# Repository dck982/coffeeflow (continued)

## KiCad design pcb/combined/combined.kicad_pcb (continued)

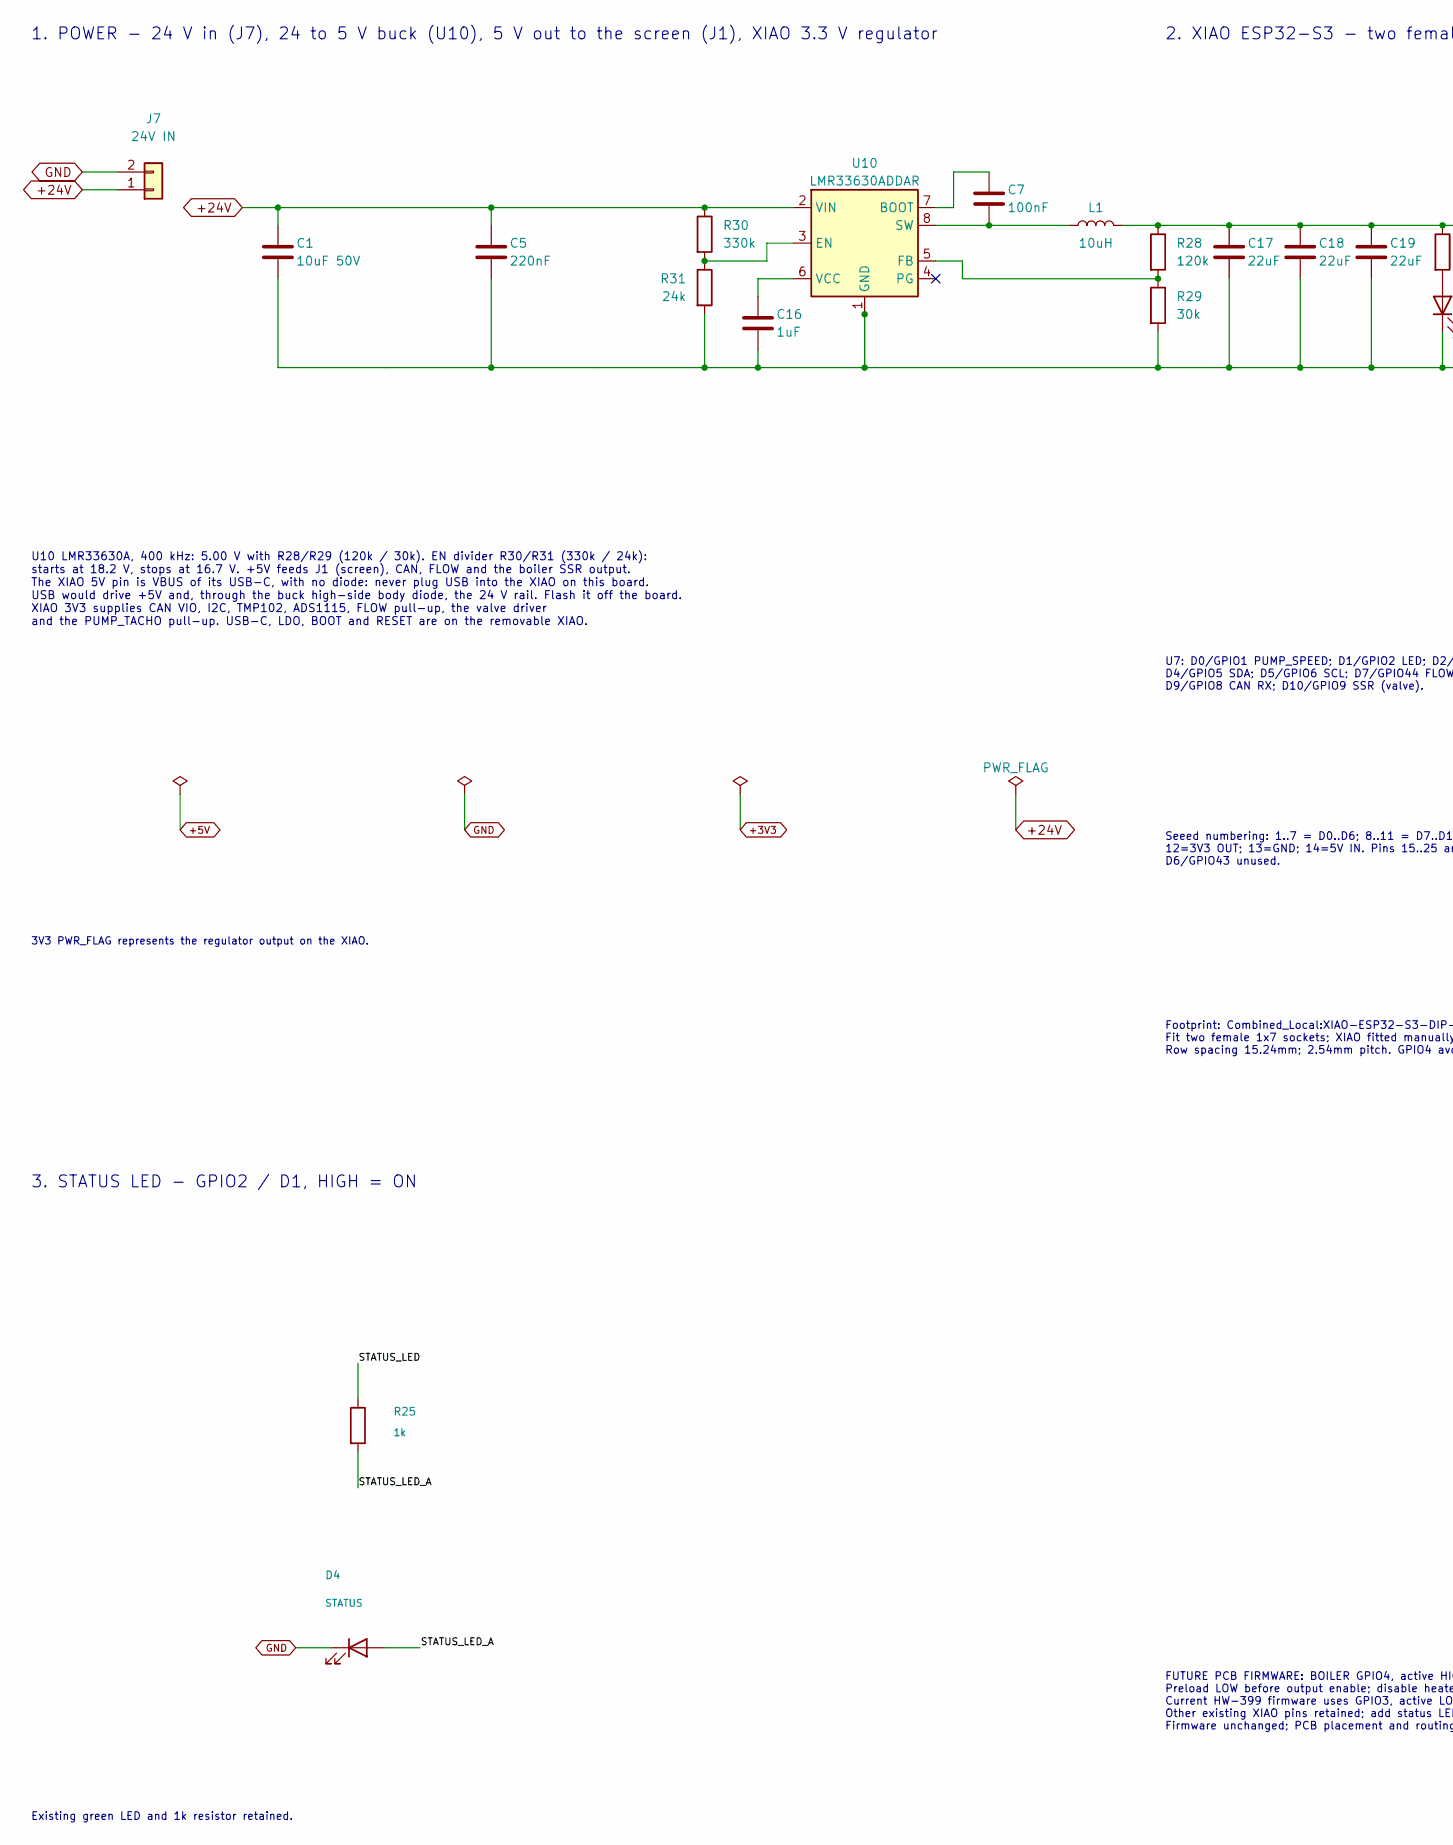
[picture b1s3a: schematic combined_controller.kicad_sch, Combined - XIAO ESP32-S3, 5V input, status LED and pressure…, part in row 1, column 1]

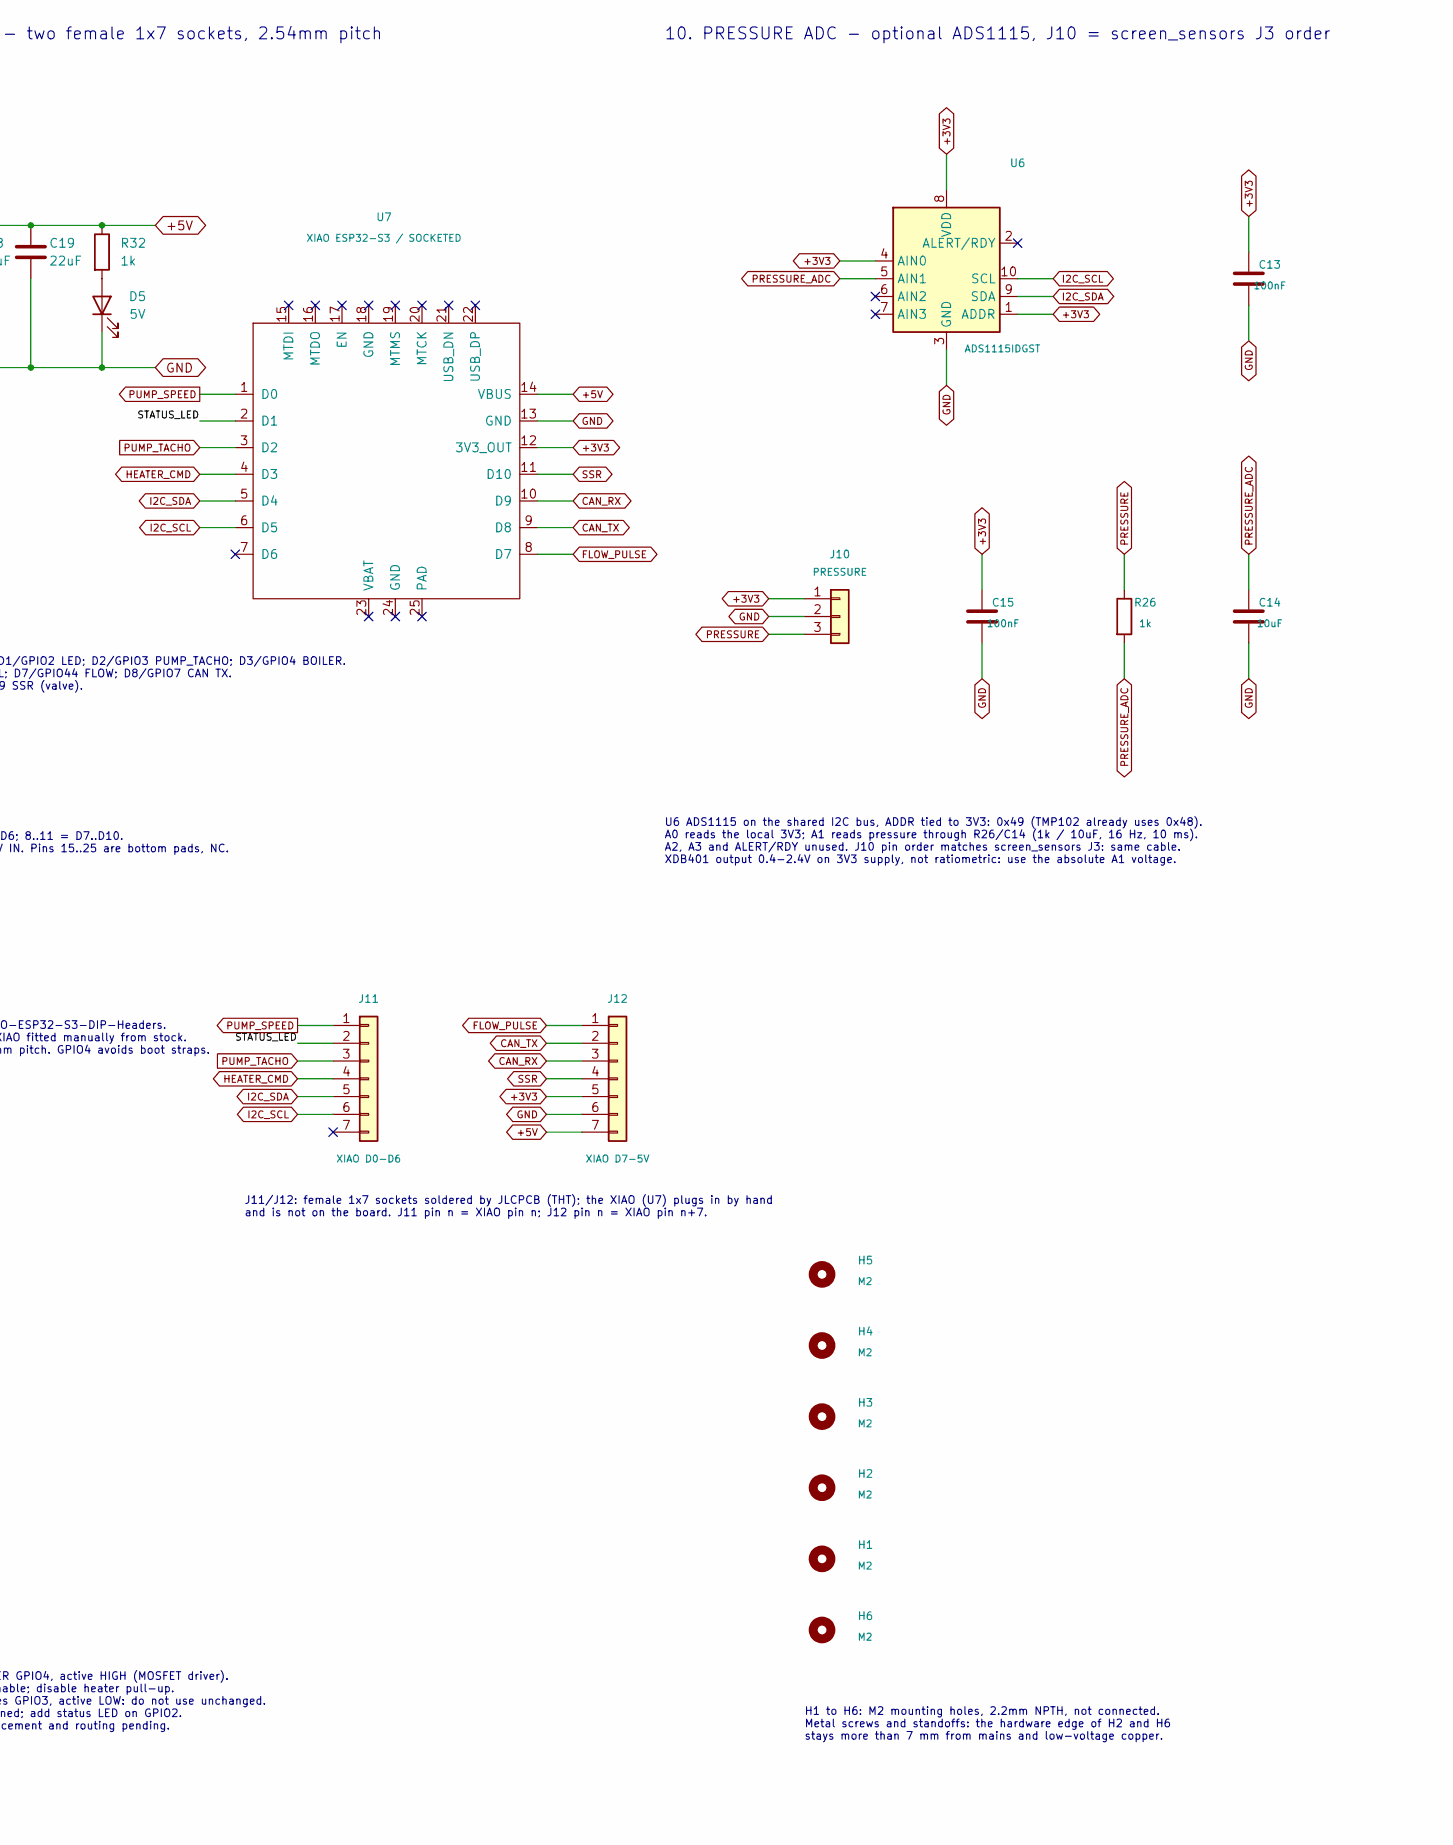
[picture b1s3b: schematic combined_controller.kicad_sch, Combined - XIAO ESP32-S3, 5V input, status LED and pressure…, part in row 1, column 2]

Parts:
C1: 10uF 50V; C_1206_3216Metric; MPN CL31A106KBHNNNE; LCSC C13585
C5: 220nF; C_0805_2012Metric; MPN CL21B224KBFNNNE; LCSC C5378
C7, C13, C15: 100nF; C_0603_1608Metric; MPN CC0603KRX7R9BB104; LCSC C14663
C14: 10uF; C_0603_1608Metric; MPN CL10A106KP8NNNC; LCSC C19702
C16: 1uF; C_0603_1608Metric; MPN CL10A105KB8NNNC; LCSC C15849
C17, C18, C19: 22uF; C_1206_3216Metric; MPN CL31A226KAHNNNE; LCSC C12891
D4: STATUS; LED_0603_1608Metric; MPN KT-0603R; LCSC C2286
D5: 5V; LED_0603_1608Metric; MPN KT-0603R; LCSC C2286
H1, H2, H3, H4, H5, H6: M2; MountingHole_2.2mm_M2; MPN M2 / 2.2mm
J7: 24V IN; CONN-TH_P3.96_HT396V-3.96-2P; MPN HT396V-3.96-2P; LCSC C577788
J10: PRESSURE; JST_XH_B3B-XH-A_1x03_P2.50mm_Vertical; MPN B3B-XH-A(LF)(SN); LCSC C144394
J11: XIAO D0-D6; XIAO_Socket_1x07_P2.54mm_Vertical; MPN HC-PM254-5.0H-1x7PZ; LCSC C27985232
J12: XIAO D7-5V; XIAO_Socket_1x07_P2.54mm_Vertical; MPN HC-PM254-5.0H-1x7PZ; LCSC C27985232
L1: 10uH; L_Changjiang_FXL0630; MPN FXL0630-100-M; LCSC C167223
R25, R26, R32: 1k; R_0603_1608Metric; MPN 0603WAF1001T5E; LCSC C21190
R28: 120k; R_0603_1608Metric; MPN 0603WAF1203T5E; LCSC C25808
R29: 30k; R_0603_1608Metric; MPN 0603WAF3002T5E; LCSC C22984
R30: 330k; R_0603_1608Metric; MPN 0603WAF3303T5E; LCSC C23137
R31: 24k; R_0603_1608Metric; MPN 0603WAF2402T5E; LCSC C23352
U6: ADS1115IDGST; TSSOP-10_3x3mm_P0.5mm; MPN ADS1115IDGST; LCSC C468683
U7: XIAO ESP32-S3 / SOCKETED; XIAO-ESP32-S3-DIP-Headers; MPN Seeed Studio XIAO ESP32-S3
U10: LMR33630ADDAR; Texas_HSOP-8-1EP_3.9x4.9mm_P1.27mm_ThermalVias; MPN LMR33630ADDAR; LCSC C841384

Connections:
+3V3: C13.1, C15.1, J10.1, J12.5, U6.1 (ADDR), U6.4 (AIN0), U6.8 (VDD), U7.12 (3V3_OUT); also elsewhere on the board
+5V: C17.1, C18.1, C19.1, J12.7, L1.2, R28.1, R32.1, U7.14 (VBUS); also elsewhere on the board
+24V: C1.1, C5.1, J7.1, R30.1, U10.2 (VIN)
/Controller/STATUS_LED: J11.2, R25.1, U7.2 (D1)
/Controller/STATUS_LED_A: D4.2 (A), R25.2
CAN_RX: J12.3, U7.10 (D9); also elsewhere on the board
CAN_TX: J12.2, U7.9 (D8); also elsewhere on the board
FLOW_PULSE: J12.1, U7.8 (D7); also elsewhere on the board
GND: C1.2, C5.2, C13.2, C14.2, C15.2, C16.2, C17.2, C18.2, C19.2, D4.1 (K), D5.1 (K), J7.2, J10.2, J12.6, R29.2, R31.2, U6.3 (GND), U7.13 (GND), U10.1 (GND), U10.9 (GND); also elsewhere on the board
HEATER_CMD: J11.4, U7.4 (D3); also elsewhere on the board
I2C_SCL: J11.6, U6.10 (SCL), U7.6 (D5); also elsewhere on the board
I2C_SDA: J11.5, U6.9 (SDA), U7.5 (D4); also elsewhere on the board
unnamed: D5.2 (A), R32.2
unnamed: C7.1, U10.7 (BOOT)
unnamed: R30.2, R31.1, U10.3 (EN)
unnamed: R28.2, R29.1, U10.5 (FB)
unnamed: C7.2, L1.1, U10.8 (SW)
unnamed: C16.1, U10.6 (VCC)
PRESSURE: J10.3, R26.1
PRESSURE_ADC: C14.1, R26.2, U6.5 (AIN1)
PUMP_SPEED: J11.1, U7.1 (D0); also elsewhere on the board
PUMP_TACHO: J11.3, U7.3 (D2); also elsewhere on the board
SSR: J12.4, U7.11 (D10); also elsewhere on the board

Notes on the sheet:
Footprint: Combined_Local:XIAO-ESP32-S3-DIP-Headers. Fit two female 1x7 sockets; XIAO fitted manually from stock. Row spacing 15.24mm; 2.54mm pitch. GPIO4 avoids boot straps.
Existing green LED and 1k resistor retained.
U7: D0/GPIO1 PUMP_SPEED; D1/GPIO2 LED; D2/GPIO3 PUMP_TACHO; D3/GPIO4 BOILER. D4/GPIO5 SDA; D5/GPIO6 SCL; D7/GPIO44 FLOW; D8/GPIO7 CAN TX. D9/GPIO8 CAN RX; D10/GPIO9 SSR (valve).
1. POWER - 24 V in (J7), 24 to 5 V buck (U10), 5 V out to the screen (J1), XIAO 3.3 V regulator
3. STATUS LED - GPIO2 / D1, HIGH = ON
3V3 PWR_FLAG represents the regulator output on the XIAO.
10. PRESSURE ADC - optional ADS1115, J10 = screen_sensors J3 order
U10 LMR33630A, 400 kHz: 5.00 V with R28/R29 (120k / 30k). EN divider R30/R31 (330k / 24k): starts at 18.2 V, stops at 16.7 V. +5V feeds J1 (screen), CAN, FLOW and the boiler SSR output. The XIAO 5V pin is VBUS of its USB-C, with no diode: never plug USB into the XIAO on this board. USB would drive 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
FUTURE PCB FIRMWARE: BOILER GPIO4, active HIGH (MOSFET driver). Preload LOW before output enable; disable heater pull-up. Current HW-399 firmware uses GPIO3, active LOW: do not use unchanged. Other existing XIAO pins retained; add status LED on GPIO2. Firmware unchanged; PCB placement and routing p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
J11/J12: female 1x7 sockets soldered by JLCPCB (THT); the XIAO (U7) plugs in by hand and is not on the board. J11 pin n = XIAO pin n; J12 pin n = XIAO pin n+7.
Seeed numbering: 1..7 = D0..D6; 8..11 = D7..D10. 12=3V3 OUT; 13=GND; 14=5V IN. Pins 15..25 are bottom pads, NC. D6/GPIO43 unused.
U6 ADS1115 on the shared I2C bus, ADDR tied to 3V3: 0x49 (TMP102 already uses 0x48). A0 reads the local 3V3; A1 reads pressure through R26/C14 (1k / 10uF, 16 Hz, 10 ms). A2, A3 and ALERT/RDY unused. J10 pin order matches screen_sensors J3: same cable. XDB401 output 0.4-2.4V on 3V3 supply, not ratio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
H1 to H6: M2 mounting holes, 2.2mm NPTH, not connected. Metal screws and standoffs: the hardware edge of H2 and H6 stays more than 7 mm from mains and low-voltage copper.
2. XIAO ESP32-S3 - two female 1x7 sockets, 2.54mm pitch

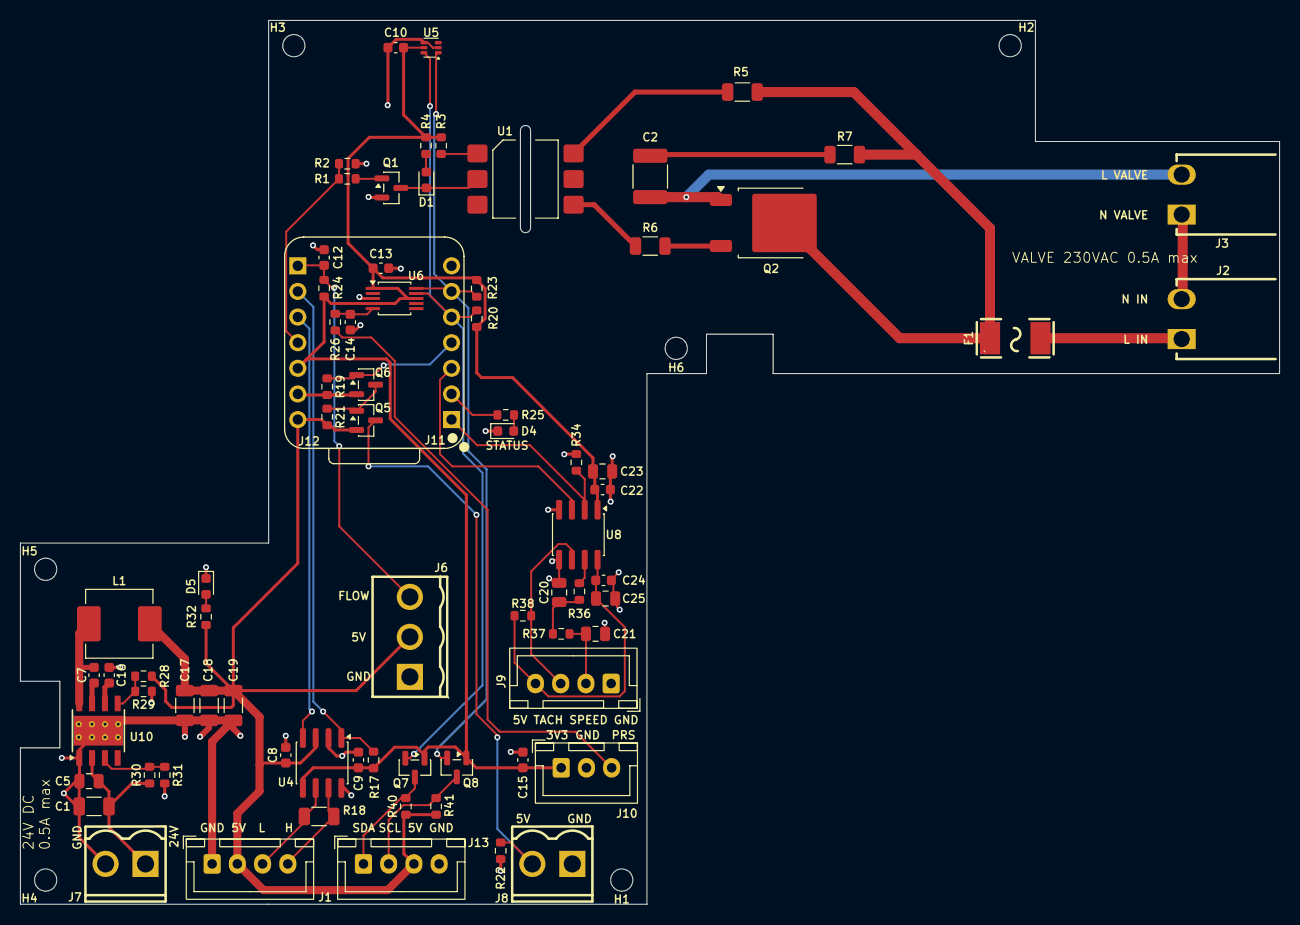
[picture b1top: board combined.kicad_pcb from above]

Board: 2 copper layers, 124.8 x 87.6 mm, 84 parts (0 on the bottom side), 47 nets.

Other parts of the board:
XIAO: XIAO-ESP32-S3-Outline

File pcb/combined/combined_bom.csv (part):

"Reference","Value","Footprint","DNP","MPN","LCSC","Note"
"C1","10uF 50V","Capacitor_SMD:C_1206_3216Metric","","CL31A106KBHNNNE","C13585","VIN ceramic, X5R 50 V 1206"
"C2","10nF 1kV","Capacitor_SMD:C_1812_4532Metric","","FV43X103K102EFG","C394164","Snubber, X7R 1000 V"
"C5","220nF","Capacitor_SMD:C_0805_2012Metric","","CL21B224KBFNNNE","C5378","VIN high-frequency bypass, 50 V X7R 0805, next to the VIN and PGND pins"
"C7","100nF","Capacitor_SMD:C_0603_1608Metric","","CC0603KRX7R9BB104","C14663","BOOT to SW"
"C8","100nF","Capacitor_SMD:C_0603_1608Metric","","CC0603KRX7R9BB104","C14663","Unpolarized capacitor"
"C9","100nF","Capacitor_SMD:C_0603_1608Metric","","CC0603KRX7R9BB104","C14663","Unpolarized capacitor"
"C10","100nF","Capacitor_SMD:C_0603_1608Metric","","CC0603KRX7R9BB104","C14663","Unpolarized capacitor"
"C12","10nF","Capacitor_SMD:C_0603_1608Metric","","0603B103K500NT","C57112","Unpolarized capacitor"
"C13","100nF","Capacitor_SMD:C_0603_1608Metric","","CC0603KRX7R9BB104","C14663","100nF 50V X7R 0603; U6 ADS1115 decoupling."
"C14","10uF","Capacitor_SMD:C_0603_1608Metric","","CL10A106KP8NNNC","C19702","10uF 10V X5R 0603; pressure input filter with R26 (16 Hz)."
"C15","100nF","Capacitor_SMD:C_0603_1608Metric","","CC0603KRX7R9BB104","C14663","100nF 50V X7R 0603; decoupling at the J10 pressure sensor supply."
"C16","1uF","Capacitor_SMD:C_0603_1608Metric","","CL10A105KB8NNNC","C15849","VCC (internal LDO) decoupling"
"C17","22uF","Capacitor_SMD:C_1206_3216Metric","","CL31A226KAHNNNE","C12891","Output ceramic, X5R 25 V 1206"
"C18","22uF","Capacitor_SMD:C_1206_3216Metric","","CL31A226KAHNNNE","C12891","Output ceramic, X5R 25 V 1206"
"C19","22uF","Capacitor_SMD:C_1206_3216Metric","","CL31A226KAHNNNE","C12891","Output ceramic, X5R 25 V 1206"
"C20","2.2uF","Capacitor_SMD:C_0805_2012Metric","","CL21A225KBQNNNE","C377773","Setpoint filter, 50 V X5R"
"C21","2.2uF","Capacitor_SMD:C_0805_2012Metric","","CL21A225KBQNNNE","C377773","Setpoint filter, 50 V X5R"
"C22","100nF","Capacitor_SMD:C_0603_1608Metric","","CC0603KRX7R9BB104","C14663","U8 VDDA (3V3) decoupling, at pin 1"
"C23","1uF","Capacitor_SMD:C_0805_2012Metric","","CL21B105KBFNNNE","C28323","U8 VDDA (3V3) decoupling, next to C22"
"C24","100nF","Capacitor_SMD:C_0603_1608Metric","","CC0603KRX7R9BB104","C14663","U8 VDDB (pump 5 V) decoupling, at pin 8"
"C25","1uF","Capacitor_SMD:C_0805_2012Metric","","CL21B105KBFNNNE","C28323","U8 VDDB (pump 5 V) decoupling, next to C24"
"D1","RED","LED_SMD:LED_0603_1608Metric","","KT-0603R","C2286","Channel indicator"
"D4","STATUS","LED_SMD:LED_0603_1608Metric","","KT-0603R","C2286","Red 0603, as D1 and D2; pin 1 cathode to GND, pin 2 anode via R25 (1k) from GPIO2."
"D5","5V","LED_SMD:LED_0603_1608Metric","","KT-0603R","C2286","Red 0603, lit while +5V is up"
"F1","0.5A 250V fast","Combined_Local:F2410","","MF2410F0.500TM","C91409","AEM 2410 fast, 100 A breaking at 250 VAC; valve only (65 mA)"
"J1","SCREEN","Connector_JST:JST_XH_B4B-XH-A_1x04_P2.50mm_Vertical","","B4B-XH-A(LF)(SN)","C144395","5 V and CAN to the screen, one cable: 1 GND, 2 +5V, 3 CAN_L, 4 CAN_H"
"J2","MAINS_IN","Combined_Local:CONN-TH_P3.96_HT396R-3.96-2P","","MXHT396R-3.96-02P-OE01-Cu-A","C48688287","1 L, 2 N"
"J3","VALVE","Combined_Local:CONN-TH_P3.96_HT396R-3.96-2P","","MXHT396R-3.96-02P-OE01-Cu-A","C48688287","1 N, 2 L (switched): N next to N of J2"
"J6","FLOW HALL","Combined_Local:CONN-TH_P3.96_HT396V-3.96-3P","","HT396V-3.96-3P","C577789","Kefa HT396V vertical header; mating plug HT396K-3.96-3P (C577778, screw) takes the 0.5 mm2 wires of the Digmesa cable: 1 GND, 2 +5V, 3 FLOW_PULSE"
"J7","24V IN","Combined_Local:CONN-TH_P3.96_HT396V-3.96-2P","","HT396V-3.96-2P","C577788","Kefa HT396V vertical header; mating plug HT396K-3.96-2P (C577777, screw), 1 +24V, 2 GND, from the Wago split of the 24 V supply"
"J8","BOILER SSR","Combined_Local:CONN-TH_P3.96_HT396V-3.96-2P","","HT396V-3.96-2P","C577788","Kefa HT396V vertical header; mating plug HT396K-3.96-2P (C577777, screw, up to 1.5 mm2) takes the 0.75 mm2 wires to the boiler SSR: 1 SSR (-), 2 SSR (+)"
"J9","PUMP","Connector_JST:JST_XH_B4B-XH-A_1x04_P2.50mm_Vertical","","B4B-XH-A(LF)(SN)","C144395","1 GND_P (green), 2 SPEED_P (brown), 3 TACHO_P (blue), 4 +5V_P (yellow); pump side only"
"J10","PRESSURE","Connector_JST:JST_XH_B3B-XH-A_1x03_P2.50mm_Vertical","","B3B-XH-A(LF)(SN)","C144394","Pressure sensor input: pin 1 3V3, 2 GND, 3 output."
"J11","XIAO D0-D6","Combined_Local:XIAO_Socket_1x07_P2.54mm_Vertical","","HC-PM254-5.0H-1x7PZ","C27985232","Female 1x7 2.54 mm socket, 5.0 mm high, for XIAO pins 1-7. Soldered by JLCPCB (THT); the XIAO plugs in by hand."
"J12","XIAO D7-5V","Combined_Local:XIAO_Socket_1x07_P2.54mm_Vertical","","HC-PM254-5.0H-1x7PZ","C27985232","Female 1x7 2.54 mm socket, 5.0 mm high, for XIAO pins 8-14. Soldered by JLCPCB (THT); the XIAO plugs in by hand."
"J13","SCALE","Connector_JST:JST_XH_B4B-XH-A_1x04_P2.50mm_Vertical","","B4B-XH-A(LF)(SN)","C144395","To the scale board J1 (screw terminal), pin for pin: 1 SCALE_SDA, 2 SCALE_SCL, 3 +5V, 4 GND; 5 V I2C to the NAU7802"
"L1","10uH","Inductor_SMD:L_Changjiang_FXL0630","","FXL0630-100-M","C167223","10 uH, 4.5 A saturation, 68 mOhm"
"Q1","SS8050","Package_TO_SOT_SMD:SOT-23","","SS8050 (Y1)","C2150","SOT-23 pinout 1 B, 2 E, 3 C"
"Q2","BT136S","Package_TO_SOT_SMD:TO-252-2","","BT136S","C23427","DPAK: 1 MT1, 2 MT2 (tab), 3 G"
"Q5","AO3401A","Package_TO_SOT_SMD:SOT-23","","AO3401A","C15127","-4.0A Id, -30V Vds, P-Channel MOSFET, SOT-23"
"Q6","2N7002","Package_TO_SOT_SMD:SOT-23","","2N7002","C8545","0.115A Id, 60V Vds, N-Channel MOSFET, SOT-23"
"Q7","BSS138","Package_TO_SOT_SMD:SOT-23","","BSS138-7-F","C40912","I2C_SDA level shifter, gate on +3V3: 3.3 V bus to SCALE_SDA (5 V)"
"Q8","BSS138","Package_TO_SOT_SMD:SOT-23","","BSS138-7-F","C40912","I2C_SCL level shifter, gate on +3V3: 3.3 V bus to SCALE_SCL (5 V)"
"R1","1k","Resistor_SMD:R_0603_1608Metric","","0603WAF1001T5E","C21190","Base resistor"
"R2","4.7k","Resistor_SMD:R_0603_1608Metric","","0603WAF4701T5E","C23162","Holds the valve channel off while the XIAO is absent or booting"
"R3","150","Resistor_SMD:R_0603_1608Metric","","0603WAF1500T5E","C22808","MOC LED: (3.3-1.2-0.1)/150 = 13 mA typ, >= 9.6 mA worst case"
"R4","1k","Resistor_SMD:R_0603_1608Metric","","0603WAF1001T5E","C21190","Indicator LED ~1.2 mA"
"R5","300","Resistor_SMD:R_1206_3216Metric","","1206W4F3000T5E","C17887","MT2 series resistor; R5 + R6 = 600 ohms"
"R6","300","Resistor_SMD:R_1206_3216Metric","","1206W4F3000T5E","C17887","Gate series resistor; R5 + R6 = 600 ohms"
"R7","100","Resistor_SMD:R_1206_3216Metric","","1206W4F1000T5E","C17901","Snubber"
"R17","10k","Resistor_SMD:R_0603_1608Metric","","0603WAF1002T5E","C25804","Resistor"
"R18","120 / 0.25W","Resistor_SMD:R_1206_3216Metric","","1206W4F1200T5E","C17909","Resistor"
"R19","100k","Resistor_SMD:R_0603_1608Metric","","0603WAF1003T5E","C25803","Resistor"
"R20","4.7k","Resistor_SMD:R_0603_1608Metric","","0603WAF4701T5E","C23162","Resistor"
"R21","10k","Resistor_SMD:R_0603_1608Metric","","0603WAF1002T5E","C25804","Resistor"
"R22","1k","Resistor_SMD:R_0603_1608Metric","","0603WAF1001T5E","C21190","Resistor"
"R23","4.7k","Resistor_SMD:R_0603_1608Metric","","0603WAF4701T5E","C23162","Resistor"
"R24","1k","Resistor_SMD:R_0603_1608Metric","","0603WAF1001T5E","C21190","Resistor"
"R25","1k","Resistor_SMD:R_0603_1608Metric","","0603WAF1001T5E","C21190","Resistor"
"R26","1k","Resistor_SMD:R_0603_1608Metric","","0603WAF1001T5E","C21190","1k 1% 0603; pressure input filter with C14."
"R28","120k","Resistor_SMD:R_0603_1608Metric","","0603WAF1203T5E","C25808","FB divider top: 1.0 V x (1 + 120/30) = 5.00 V"
"R29","30k","Resistor_SMD:R_0603_1608Metric","","0603WAF3002T5E","C22984","FB divider bottom"
"R30","330k","Resistor_SMD:R_0603_1608Metric","","0603WAF3303T5E","C23137","EN divider top: starts at 18.2 V, stops at 16.7 V"
"R31","24k","Resistor_SMD:R_0603_1608Metric","","0603WAF2402T5E","C23352","EN divider bottom"
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
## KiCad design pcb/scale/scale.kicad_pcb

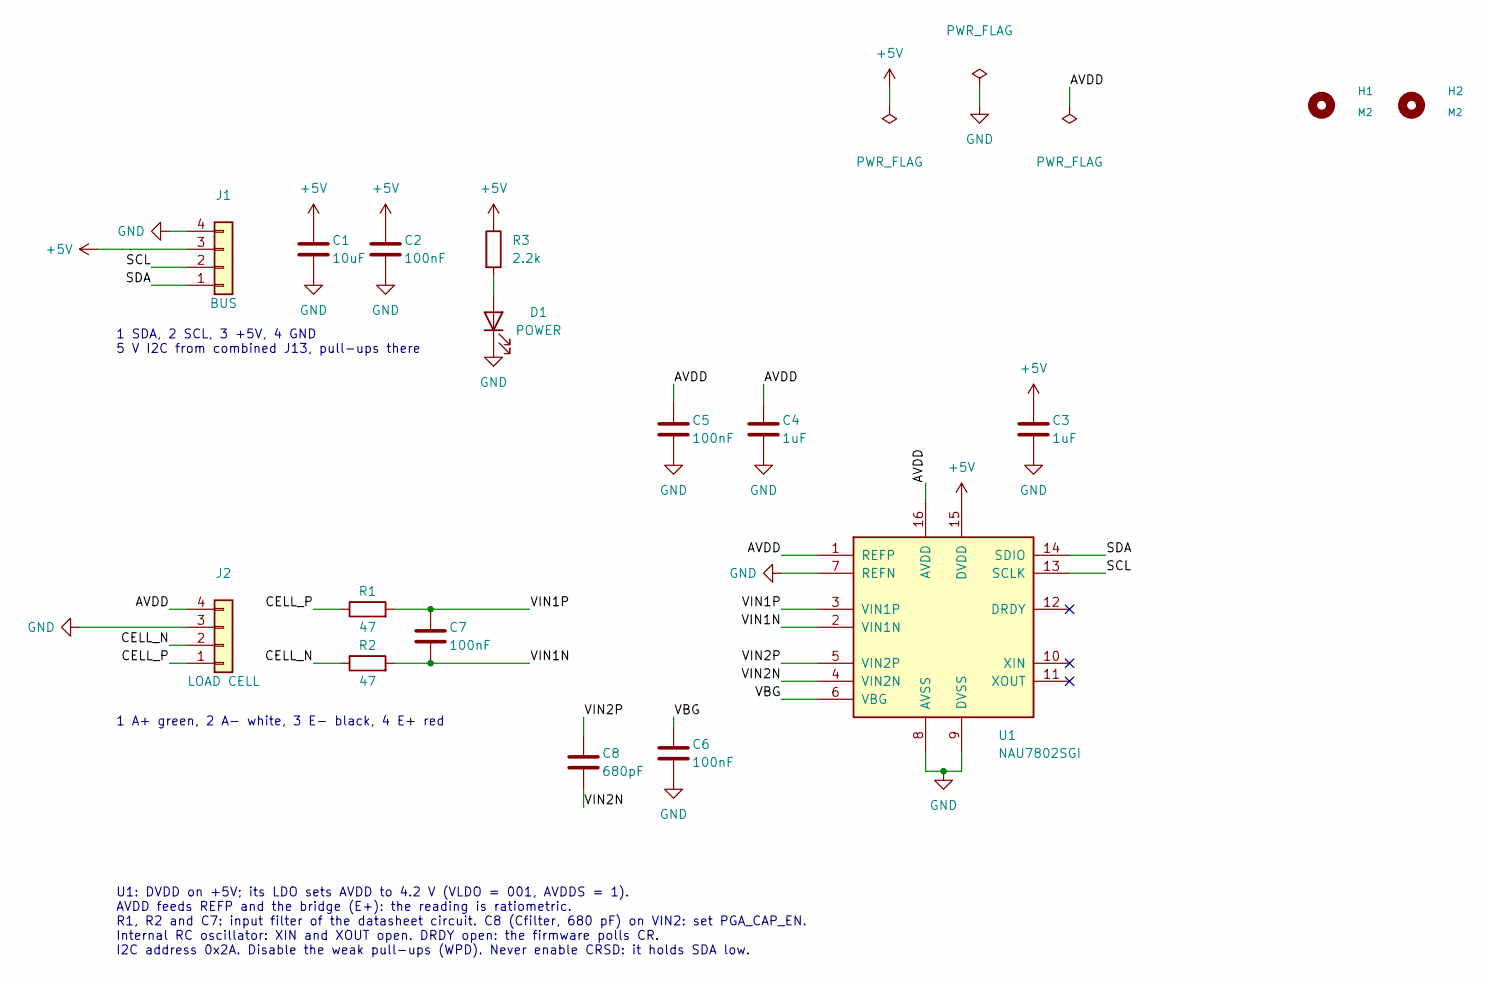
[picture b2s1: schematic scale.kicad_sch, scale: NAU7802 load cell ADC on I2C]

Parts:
C1: 10uF; C_0805_2012Metric; MPN CL21A106KAYNNNE; LCSC C15850
C2, C5, C6, C7: 100nF; C_0603_1608Metric; MPN CC0603KRX7R9BB104; LCSC C14663
C3, C4: 1uF; C_0603_1608Metric; MPN CL10A105KB8NNNC; LCSC C15849
C8: 680pF; C_0603_1608Metric; MPN 0603B681K500NT; LCSC C1630
D1: POWER; LED_0603_1608Metric; MPN KT-0603R; LCSC C2286
H1, H2: M2; MountingHole_2.2mm_M2; MPN M2 / 2.2mm
J1: BUS; TerminalBlock_Dorabo_DB125-2.54-4P_1x04_P2.54mm_Horizontal; MPN DB125-2.54-4P-GN-S; LCSC C918122
J2: LOAD CELL; TerminalBlock_Dorabo_DB125-2.54-4P_1x04_P2.54mm_Horizontal; MPN DB125-2.54-4P-GN-S; LCSC C918122
R1, R2: 47; R_0603_1608Metric; MPN 0603WAF470JT5E; LCSC C23182
R3: 2.2k; R_0603_1608Metric; MPN 0603WAF2201T5E; LCSC C4190
U1: NAU7802SGI; SOIC-16_3.9x9.9mm_P1.27mm; MPN NAU7802SGI; LCSC C2614351

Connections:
+5V: C1.1, C2.1, C3.1, J1.3, R3.1, U1.15 (DVDD)
/AVDD: C4.1, C5.1, J2.4, U1.1 (REFP), U1.16 (AVDD)
/CELL_N: J2.2, R2.1
/CELL_P: J2.1, R1.1
/SCL: J1.2, U1.13 (SCLK)
/SDA: J1.1, U1.14 (SDIO)
/VBG: C6.1, U1.6 (VBG)
/VIN1N: C7.2, R2.2, U1.2 (VIN1N)
/VIN1P: C7.1, R1.2, U1.3 (VIN1P)
/VIN2N: C8.2, U1.4 (VIN2N)
/VIN2P: C8.1, U1.5 (VIN2P)
GND: C1.2, C2.2, C3.2, C4.2, C5.2, C6.2, D1.1 (K), J1.4, J2.3, U1.7 (REFN), U1.8 (AVSS), U1.9 (DVSS)
unnamed: D1.2 (A), R3.2

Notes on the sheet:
1 SDA, 2 SCL, 3 +5V, 4 GND 5 V I2C from combined J13, pull-ups there
1 A+ green, 2 A- white, 3 E- black, 4 E+ red
U1: DVDD on +5V; its LDO sets AVDD to 4.2 V (VLDO = 001, AVDDS = 1). AVDD feeds REFP and the bridge (E+): the reading is ratiometric. R1, R2 and C7: input filter of the datasheet circuit. C8 (Cfilter, 680 pF) on VIN2: set PGA_CAP_EN. Internal RC oscillator: XIN and XOUT open. DRDY open: the firmwar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

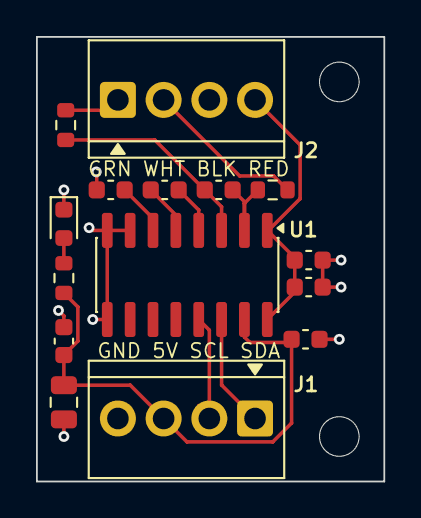
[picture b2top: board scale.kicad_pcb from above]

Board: 2 copper layers, 19.3 x 24.7 mm, 17 parts (0 on the bottom side), 13 nets.

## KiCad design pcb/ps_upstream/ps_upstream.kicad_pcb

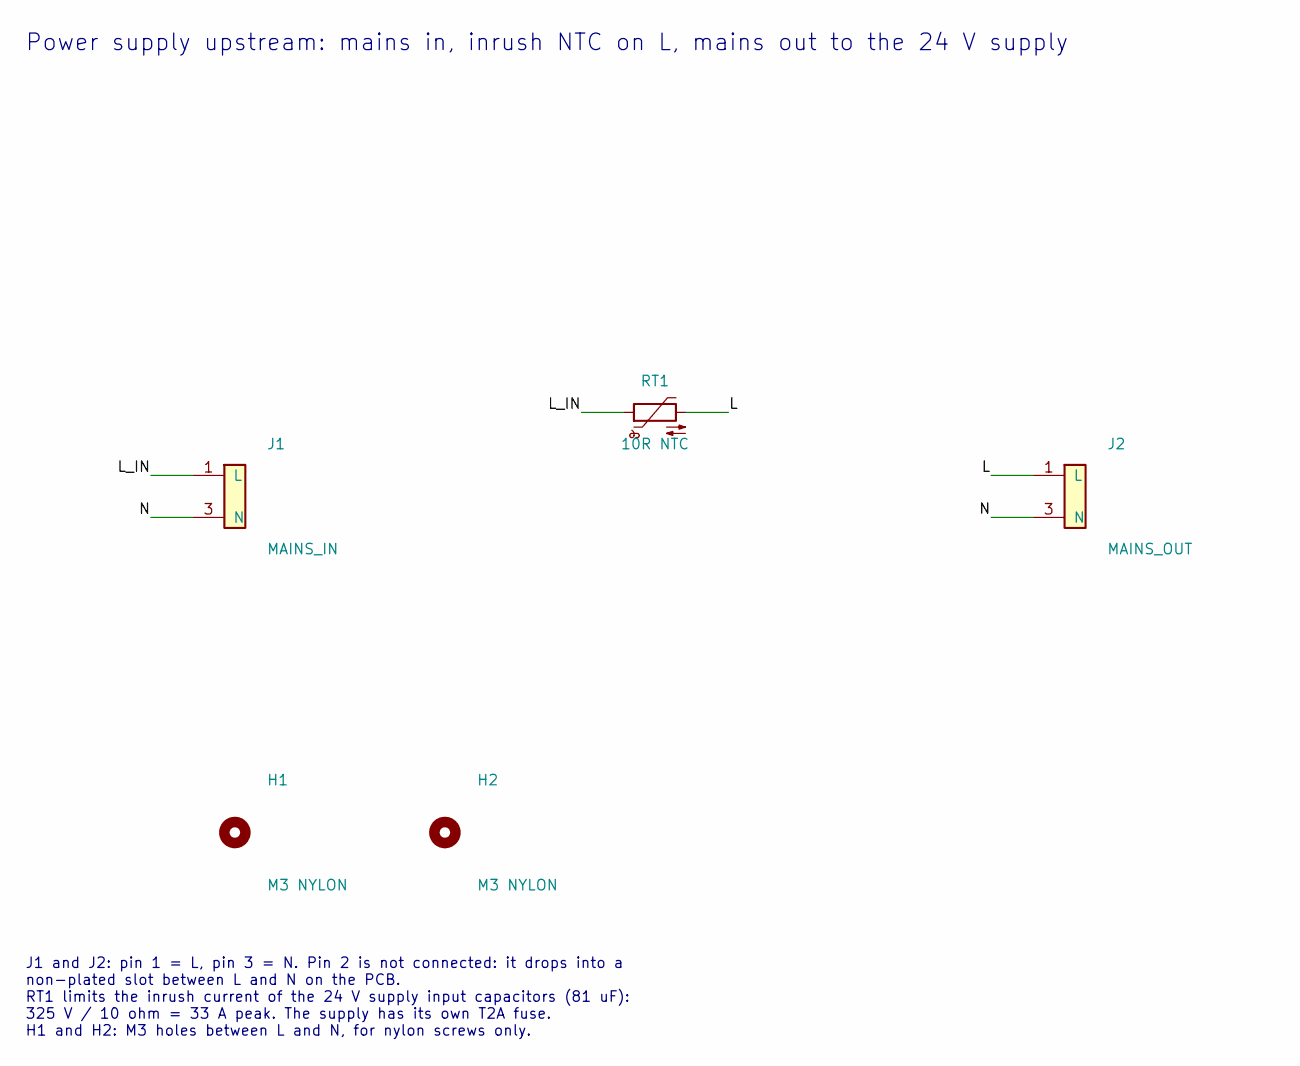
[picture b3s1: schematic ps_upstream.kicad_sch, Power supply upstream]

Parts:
H1, H2: M3 NYLON; MountingHole_3.2mm_M3_Nylon
J1: MAINS_IN; HT396R-3.96-3P_Pin2Slot; MPN HT396R-3.96-3P; LCSC C577800
J2: MAINS_OUT; VH-3A_Pin2Slot; MPN VH-3A; LCSC C20547
RT1: 10R NTC; NTC_TDK_S236_P5.00; MPN B57236S0100M000; LCSC C125458

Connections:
/L: J2.1 (L), RT1.2
/L_IN: J1.1 (L), RT1.1
/N: J1.3 (N), J2.3 (N)

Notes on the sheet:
Power supply upstream: mains in, inrush NTC on L, mains out to the 24 V supply
J1 and J2: pin 1 = L, pin 3 = N. Pin 2 is not connected: it drops into a non-plated slot between L and N on the PCB. RT1 limits the inrush current of the 24 V supply input capacitors (81 uF): 325 V / 10 ohm = 33 A peak. The supply has its own T2A fuse. H1 and H2: M3 holes between L and N, for nylon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

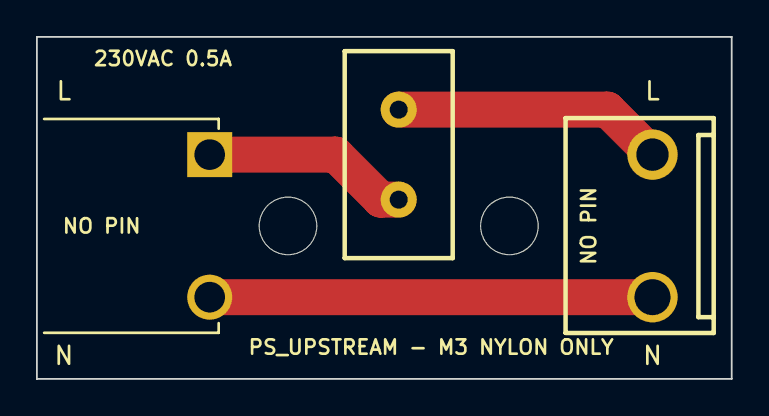
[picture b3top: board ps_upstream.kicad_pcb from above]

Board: 2 copper layers, 38.6 x 19.0 mm, 5 parts (0 on the bottom side), 3 nets.

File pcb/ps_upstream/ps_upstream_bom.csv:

Reference,Value,Footprint,DNP,LCSC,MPN,Description,Note
J1,MAINS_IN,PS_Upstream_Local:HT396R-3.96-3P_Pin2Slot,0,C577800,HT396R-3.96-3P,"Mains input, Kefa HT396R right-angle pluggable header, 3.96 mm","1 L, 2 not connected (slot), 3 N"
RT1,10R NTC,PS_Upstream_Local:NTC_TDK_S236_P5.00,0,C125458,B57236S0100M000,"Inrush current limiter, TDK S236, 10 ohm, 3.5 A, 300 uF tested at 230 V",In series with L
J2,MAINS_OUT,PS_Upstream_Local:VH-3A_Pin2Slot,0,C20547,VH-3A,"Mains output to the 24 V supply, JST VH-compatible vertical header, 3.96 mm","1 L, 2 not connected (slot), 3 N"

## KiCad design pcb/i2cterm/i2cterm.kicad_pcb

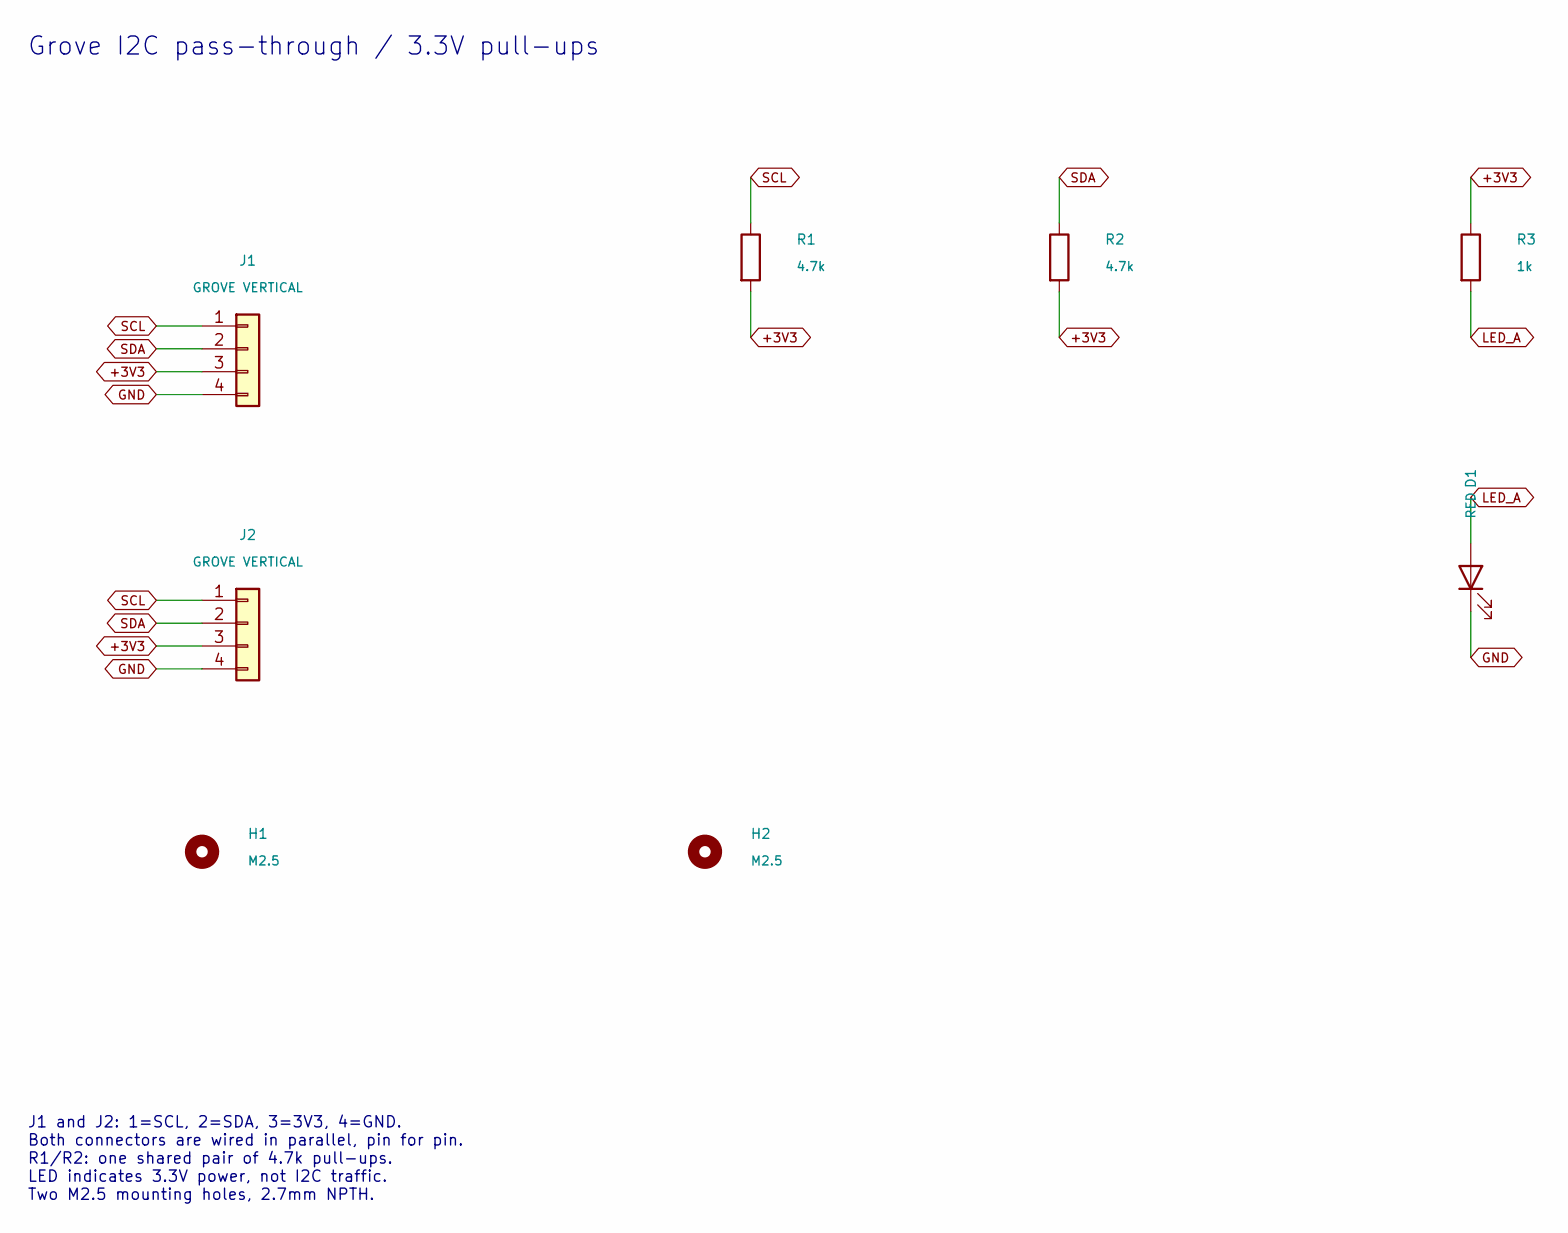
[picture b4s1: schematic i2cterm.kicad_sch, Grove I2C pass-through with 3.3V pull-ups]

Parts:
D1: RED; LED_0603_1608Metric; MPN KT-0603R; LCSC C2286
H1, H2: M2.5; MountingHole_2.7mm_M2.5; MPN M2.5 / 2.7mm
J1, J2: GROVE VERTICAL; CONN-TH_HY-4A; MPN HY-4A; LCSC C722737
R1, R2: 4.7k; R_0603_1608Metric; MPN 0603 4.7k 1%; LCSC C23162
R3: 1k; R_0603_1608Metric; MPN 0603 1k 1%; LCSC C21190

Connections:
+3V3: J1.3, J2.3, R1.2, R2.2, R3.1
GND: D1.1 (K), J1.4, J2.4
LED_A: D1.2 (A), R3.2
SCL: J1.1, J2.1, R1.1
SDA: J1.2, J2.2, R2.1

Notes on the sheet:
Grove I2C pass-through / 3.3V pull-ups
J1 and J2: 1=SCL, 2=SDA, 3=3V3, 4=GND. Both connectors are wired in parallel, pin for pin. R1/R2: one shared pair of 4.7k pull-ups. LED indicates 3.3V power, not I2C traffic. Two M2.5 mounting holes, 2.7mm NPTH.

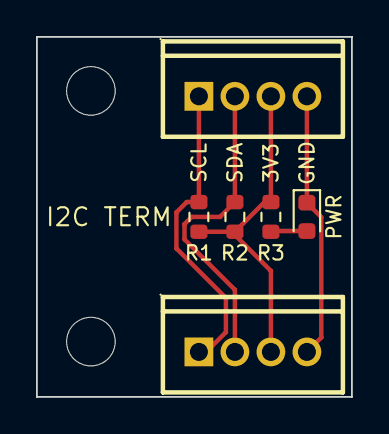
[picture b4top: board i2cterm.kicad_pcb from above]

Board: 2 copper layers, 17.5 x 20.0 mm, 8 parts (0 on the bottom side), 5 nets.

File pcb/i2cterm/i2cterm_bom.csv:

Reference,Value,Footprint,DNP,LCSC,MPN,Description,Sheet,Datasheet
J1,GROVE VERTICAL,I2CTerm_Local:CONN-TH_HY-4A,0,C722737,HY-4A,"Generic connector, single row, 01x04, script generated (kicad-library-utils/schlib/autogen/connector/)",1,https://www.lcsc.com/product-detail/C722737.html
R1,4.7k,Resistor_SMD:R_0603_1608Metric,0,C23162,0603 4.7k 1%,Resistor,1,
R2,4.7k,Resistor_SMD:R_0603_1608Metric,0,C23162,0603 4.7k 1%,Resistor,1,
R3,1k,Resistor_SMD:R_0603_1608Metric,0,C21190,0603 1k 1%,Resistor,1,
D1,RED,LED_SMD:LED_0603_1608Metric,0,C2286,KT-0603R,Light emitting diode,1,https://www.lcsc.com/datasheet/C2286.pdf
J2,GROVE VERTICAL,I2CTerm_Local:CONN-TH_HY-4A,0,C722737,HY-4A,"Generic connector, single row, 01x04, script generated (kicad-library-utils/schlib/autogen/connector/)",1,https://www.lcsc.com/product-detail/C722737.html
